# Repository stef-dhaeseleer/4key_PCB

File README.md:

# 4key_PCB
4 key PCB project based on https://github.com/ruiqimao/keyboard-pcb-guide

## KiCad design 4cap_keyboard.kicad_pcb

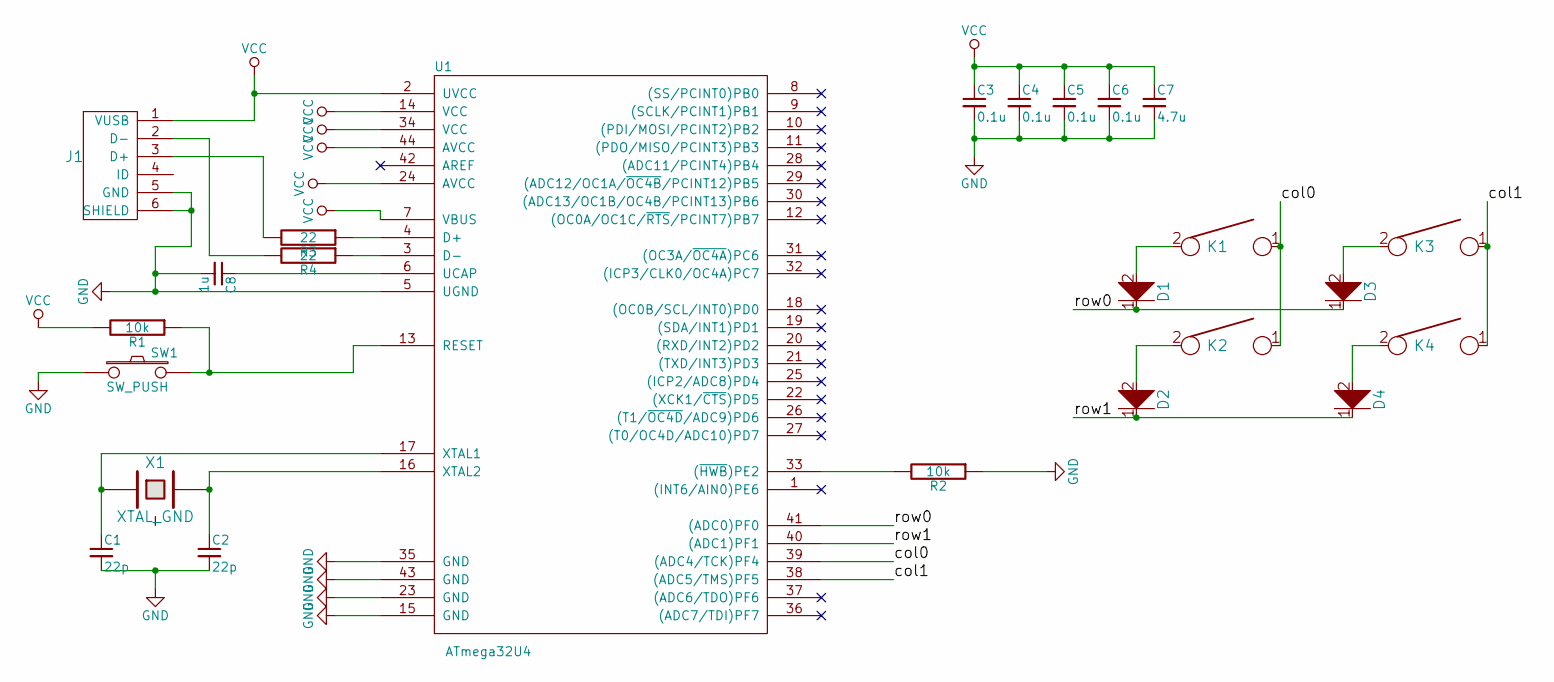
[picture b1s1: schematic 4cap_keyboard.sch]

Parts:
C1, C2: 22p; C_0805_HandSoldering
C3, C4, C5, C6: 0.1u; C_0805_HandSoldering
C7: 4.7u; C_0805_HandSoldering
C8: 1u; C_0805_HandSoldering
D1, D2, D3, D4: D; D_SOD123_axial
J1: USB_mini_micro_B; USB_miniB_hirose_5S8
K1, K2, K3, K4: KEYSW; Mx_Alps_100
R1, R2: 10k; R_0805_HandSoldering
R3, R4: 22; R_0805_HandSoldering
SW1: SW_PUSH; SW_SPST_TL3342
U1: ATmega32U4; PQFP-44_10x10mm_Pitch0.8mm
X1: XTAL_GND; crystal_FA238-TSX3225

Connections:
/col0: K1.1, K2.1, U1.39 ((ADC4/TCK)PF4)
/col1: K3.1, K4.1, U1.38 ((ADC5/TMS)PF5)
/row0: D1.1, D3.1, U1.41 ((ADC0)PF0)
/row1: D2.1, D4.1, U1.40 ((ADC1)PF1)
GND: C1.2, C2.2, C3.2, C4.2, C5.2, C6.2, C7.2, C8.2, J1.5 (GND), J1.6 (SHIELD), R2.1, SW1.1, U1.5 (UGND), U1.15 (GND), U1.23 (GND), U1.35 (GND), U1.43 (GND)
unnamed: C1.1, U1.17 (XTAL1), X1.1
unnamed: C2.1, U1.16 (XTAL2), X1.2
unnamed: C8.1, U1.6 (UCAP)
unnamed: D1.2, K1.2
unnamed: D2.2, K2.2
unnamed: D3.2, K3.2
unnamed: D4.2, K4.2
unnamed: J1.2 (D-), R4.2
unnamed: J1.3 (D+), R3.2
unnamed: R1.1, SW1.2, U1.13 (RESET)
unnamed: R2.2, U1.33 ((~HWB~)PE2)
unnamed: R3.1, U1.4 (D+)
unnamed: R4.1, U1.3 (D-)
VCC: C3.1, C4.1, C5.1, C6.1, C7.1, J1.1 (VUSB), R1.2, U1.2 (UVCC), U1.7 (VBUS), U1.14 (VCC), U1.24 (AVCC), U1.34 (VCC), U1.44 (AVCC)

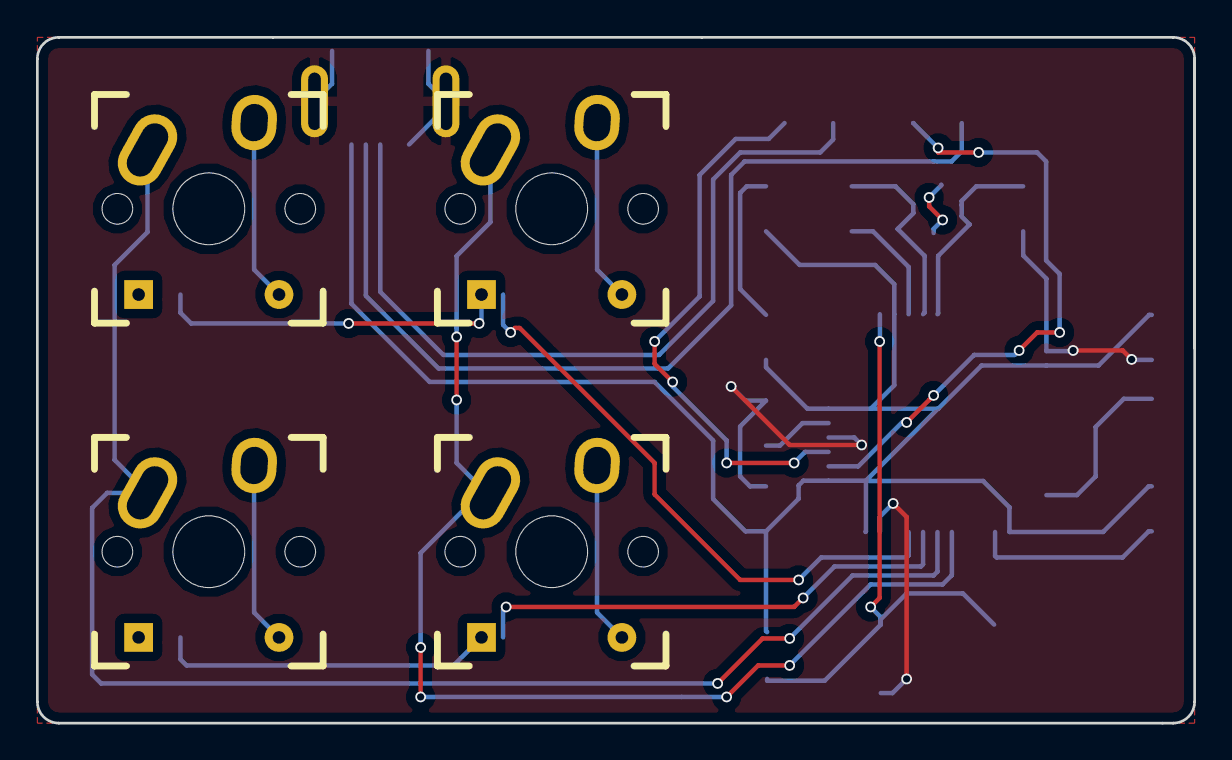
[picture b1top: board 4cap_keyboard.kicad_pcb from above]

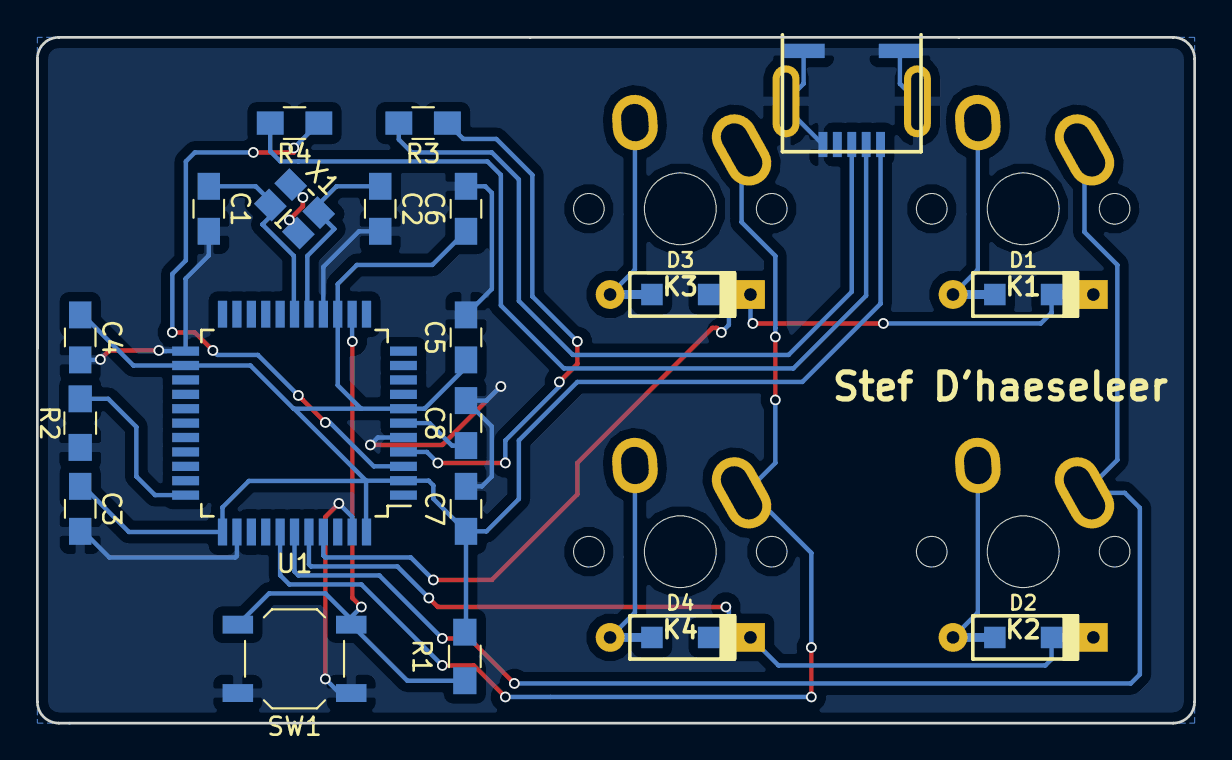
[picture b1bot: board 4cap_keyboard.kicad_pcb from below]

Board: 2 copper layers, 64.3 x 38.1 mm, 24 parts (20 on the bottom side), 19 nets.

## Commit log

2017-10-15 PCBs ordered
